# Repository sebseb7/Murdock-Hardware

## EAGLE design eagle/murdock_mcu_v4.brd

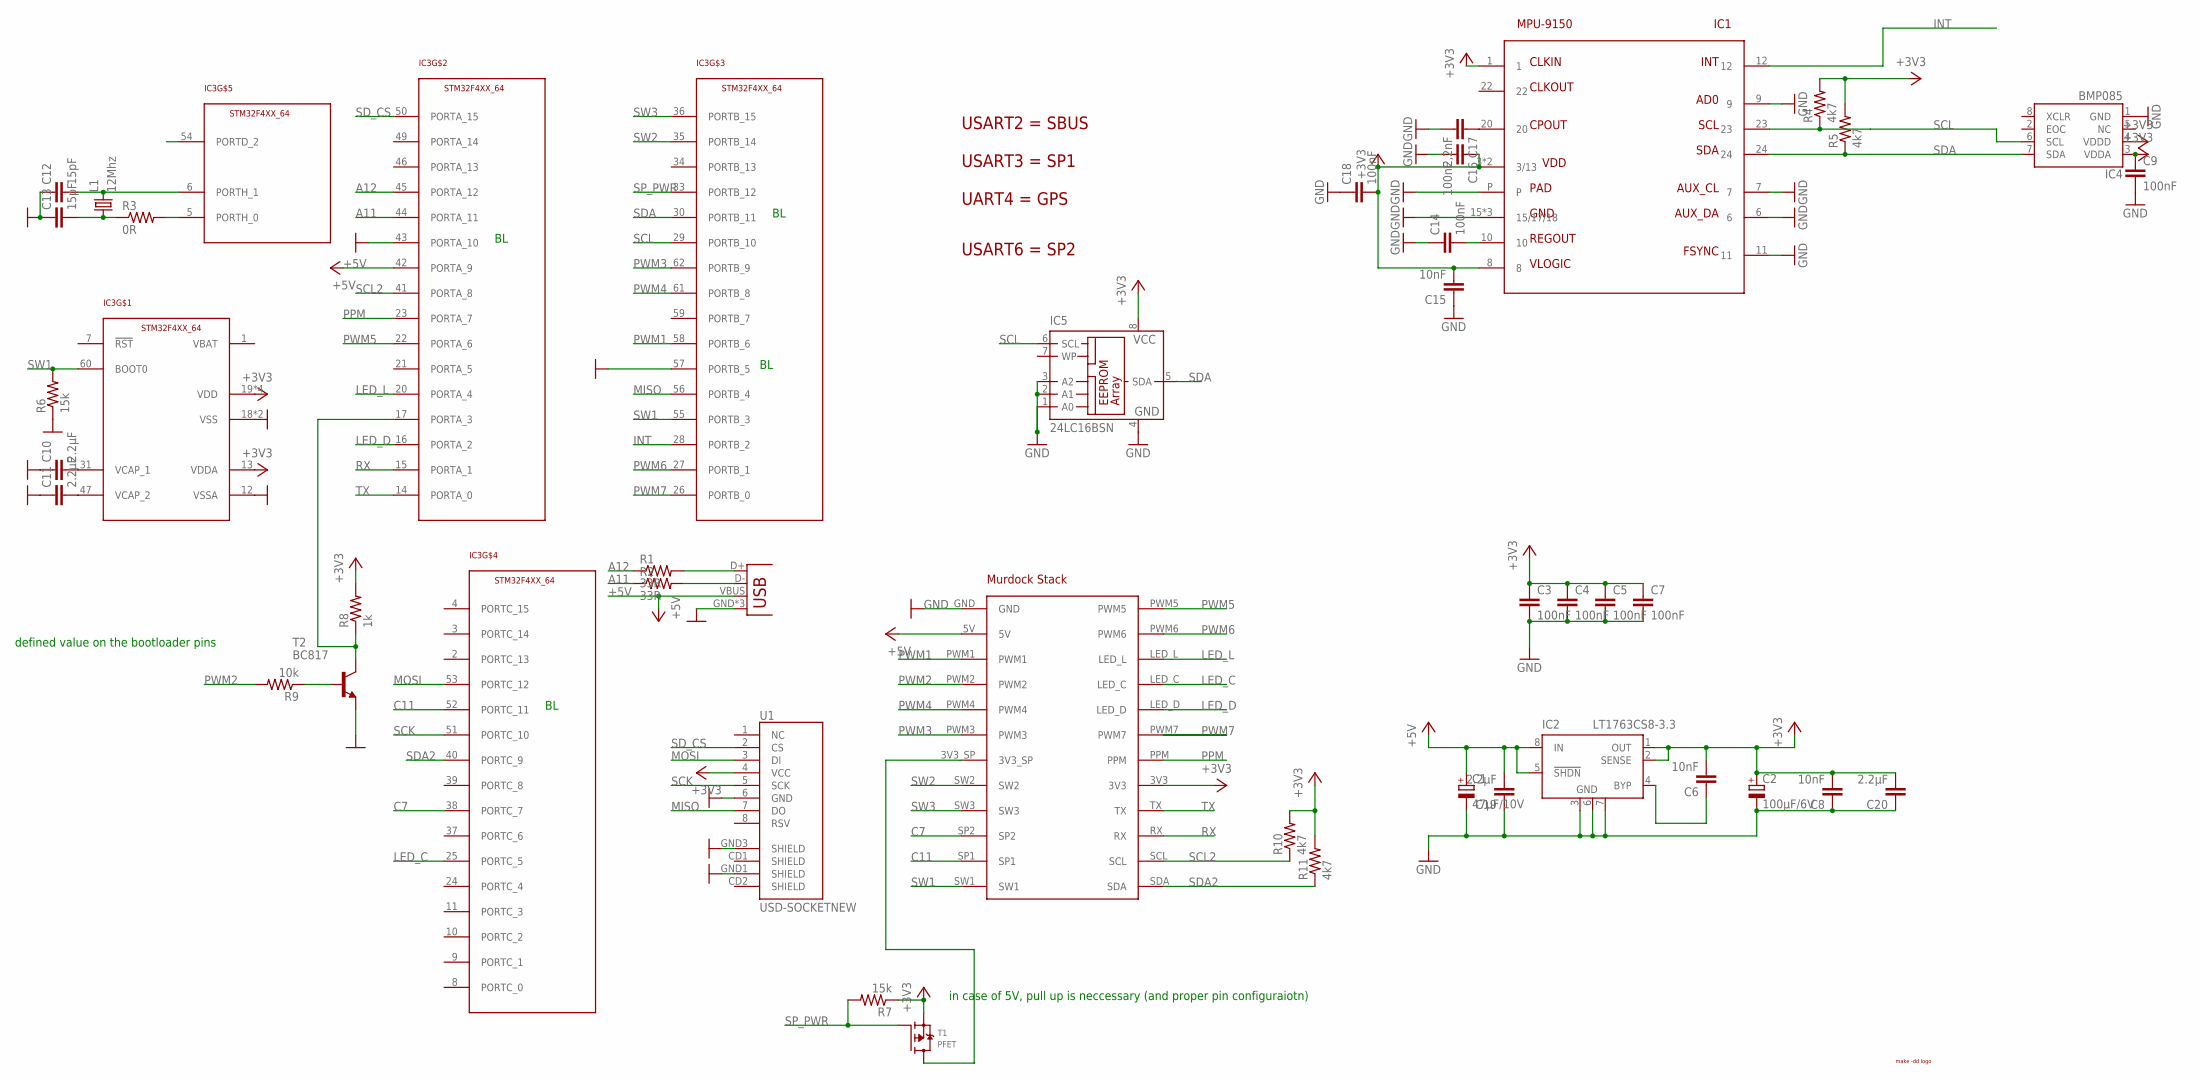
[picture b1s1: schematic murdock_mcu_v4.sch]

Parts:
C1: 47µF/10V; SMC_C
C2: 100µF/6V; SMC_C
C3, C4, C5, C7, C9, C14, C16, C18: 100nF; 0402-CAP
C6, C8: 10nF; C0402
C10, C11, C19, C20: 2.2µF; 0805
C12, C13: 15pF; 0402-CAP
C15: 10nF; 0402-CAP
C17: 2,2nF; 0402-CAP
IC1: MPU-9150; QFN24
IC2: LT1763CS8-3.3; SOIC8
IC3: STM32F4XX_64; TQFP64
IC4: BMP085
IC5: 24LC16BSN; SO-08
JP1: USB-MICROB
L1: 12Mhz; X22
R1, R2: 33R; 0402-RES
R3: 0R; 0402-RES
R4, R5, R10, R11: 4k7; 0402-RES
R6, R7: 15k; 0402-RES
R8: 1k; 0402-RES
R9: 10k; 0402-RES
T1: PFET; SOT23-R
T2: BC817; SOT23
U1: USD-SOCKETNEW; MICRO-SD-SOCKET-PP
U$1: MAKE-DD_LOGO
X2: MURDOCK_STACK

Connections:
+3V3: C2.+, C3.1, C4.1, C5.1, C6.2, C7.1, C8.2, C9.1, C15.2, C16.1, C18.2, C20.2, IC1.1, IC1.3 (3/13), IC1.8, IC1.13 (3/13), IC2.1 (OUT), IC2.2 (SENSE), IC3.13 (VDDA), IC3.19 (VDD), IC3.32 (VDD), IC3.48 (VDD), IC3.64 (VDD), IC4.3 (VDDA), IC4.4 (VDDD), IC5.8 (VCC), R4.2, R5.2, R7.1, R8.2, R10.2, R11.2, T1.2 (S), U1.4 (VCC), X2.3V3
+5V: C1.+, C19.2, IC2.5 (!SHDN), IC2.8 (IN), IC3.42 (PORTA_9), JP1.VBUS, X2.5V
A11: IC3.44 (PORTA_11), R2.1
A12: IC3.45 (PORTA_12), R1.1
C7: IC3.38 (PORTC_7), X2.SP2
C11: IC3.52 (PORTC_11), X2.SP1
GND: C1.-, C2.-, C3.2, C4.2, C5.2, C7.2, C8.1, C9.2, C10.1, C11.1, C12.1, C13.1, C14.1, C15.1, C16.2, C17.2, C18.1, C19.1, C20.1, IC1.6, IC1.7, IC1.9, IC1.11, IC1.15 (15/17/18), IC1.17 (15/17/18), IC1.18 (15/17/18), IC1.P, IC2.3 (GND), IC2.6 (GND), IC2.7 (GND), IC3.12 (VSSA), IC3.18 (VSS), IC3.43 (PORTA_10), IC3.57 (PORTB_5), IC3.63 (VSS), IC4.1 (GND), IC5.1 (A0), IC5.2 (A1), IC5.3 (A2), IC5.4 (GND), JP1.GND, JP1.MT1 (GND), JP1.MT2 (GND), R6.1, T2.2 (E), U1.6 (GND), U1.GND1 (SHIELD), U1.GND3 (SHIELD), X2.GND
INT: IC1.12, IC3.28 (PORTB_2)
LED_C: IC3.25 (PORTC_5), X2.LED_C
LED_D: IC3.16 (PORTA_2), X2.LED_D
LED_L: IC3.20 (PORTA_4), X2.LED_L
MISO: IC3.56 (PORTB_4), U1.7 (DO)
MOSI: IC3.53 (PORTC_12), U1.3 (DI)
unnamed: JP1.D-, R2.2
unnamed: JP1.D+, R1.2
unnamed: C10.2, IC3.31 (VCAP_1)
unnamed: C11.2, IC3.47 (VCAP_2)
unnamed: IC3.5 (PORTH_0), R3.2
unnamed: C13.2, L1.1, R3.1
unnamed: C12.2, IC3.6 (PORTH_1), L1.3 (2)
unnamed: T1.3 (D), X2.3V3_SP
unnamed: C14.2, IC1.10
unnamed: C17.1, IC1.20
unnamed: IC3.17 (PORTA_3), R8.1, T2.3 (C)
unnamed: R9.1, T2.1 (B)
unnamed: C6.1, IC2.4 (BYP)
PPM: IC3.23 (PORTA_7), X2.PPM
PWM1: IC3.58 (PORTB_6), X2.PWM1
PWM2: R9.2, X2.PWM2
PWM3: IC3.62 (PORTB_9), X2.PWM3
PWM4: IC3.61 (PORTB_8), X2.PWM4
PWM5: IC3.22 (PORTA_6), X2.PWM5
PWM6: IC3.27 (PORTB_1), X2.PWM6
PWM7: IC3.26 (PORTB_0), X2.PWM7
RX: IC3.15 (PORTA_1), X2.RX
SCK: IC3.51 (PORTC_10), U1.5 (SCK)
SCL: IC1.23, IC3.29 (PORTB_10), IC4.6 (SCL), IC5.6 (SCL), R4.1
SCL2: IC3.41 (PORTA_8), R10.1, X2.SCL
SDA: IC1.24, IC3.30 (PORTB_11), IC4.7 (SDA), IC5.5 (SDA), R5.1
SDA2: IC3.40 (PORTC_9), R11.1, X2.SDA
SD_CS: IC3.50 (PORTA_15), U1.2 (CS)
SP_PWR: IC3.33 (PORTB_12), R7.2, T1.1 (G)
SW1: IC3.55 (PORTB_3), IC3.60 (BOOT0), R6.2, X2.SW1
SW2: IC3.35 (PORTB_14), X2.SW2
SW3: IC3.36 (PORTB_15), X2.SW3
TX: IC3.14 (PORTA_0), X2.TX

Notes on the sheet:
defined value on the bootloader pins
UART4 = GPS
USART2 = SBUS
USART6 = SP2
USART3 = SP1
in case of 5V, pull up is neccessary (and proper pin configuraiotn)

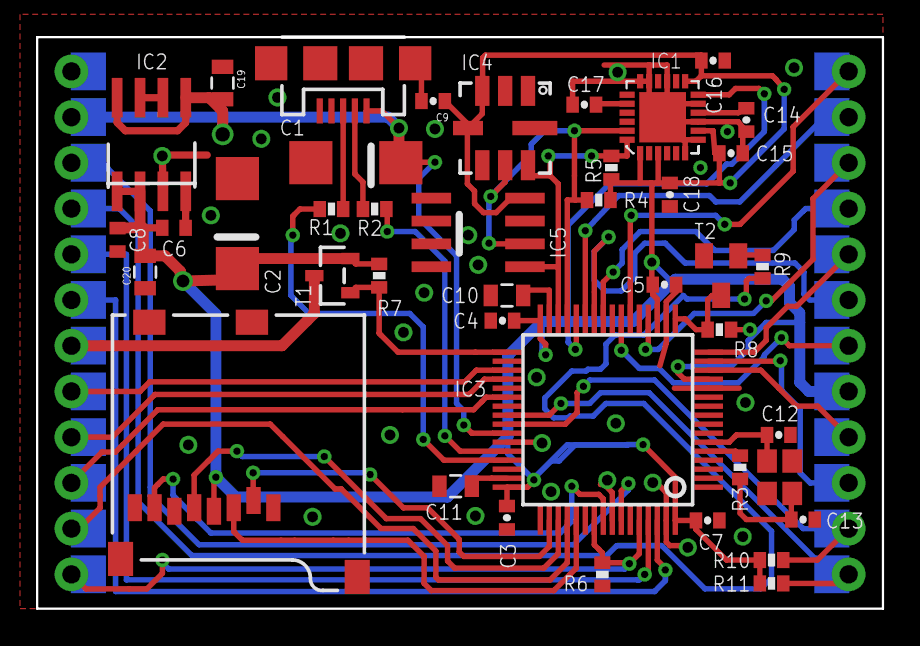
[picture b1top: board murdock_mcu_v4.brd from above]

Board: 2 copper layers, 47.0 x 31.8 mm, 43 parts (1 on the bottom side), 46 nets.

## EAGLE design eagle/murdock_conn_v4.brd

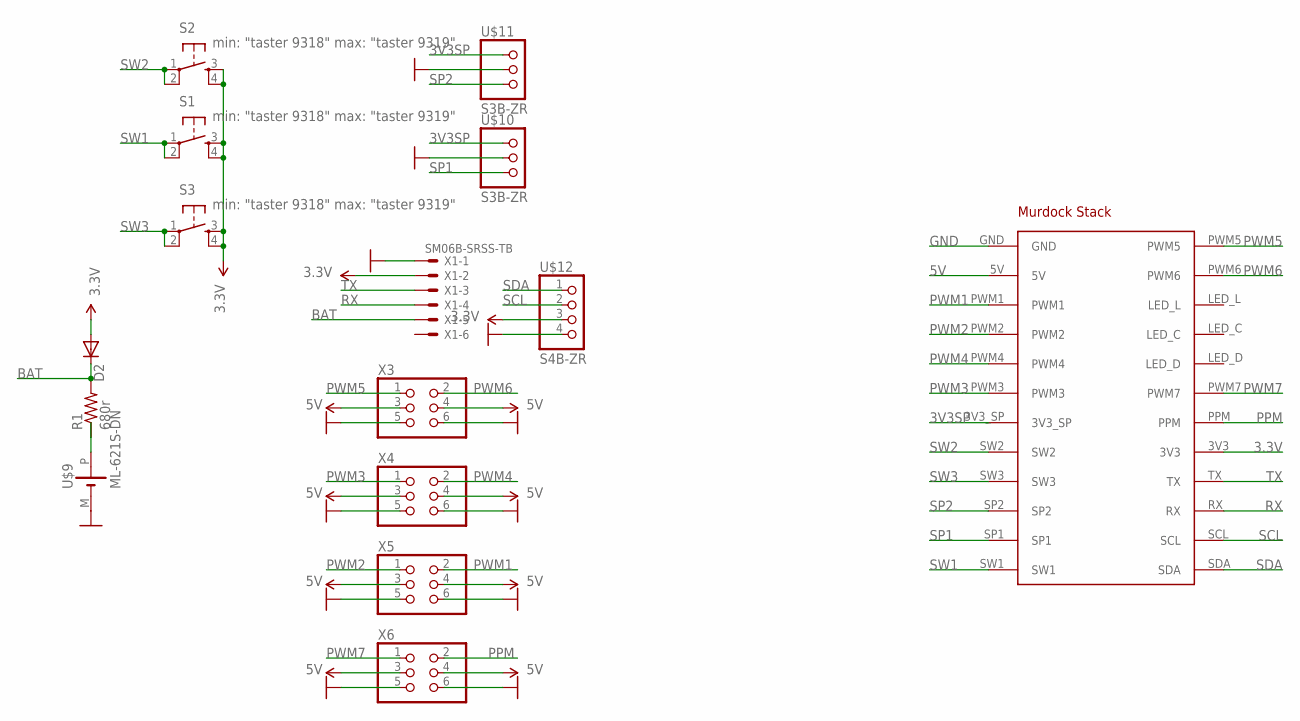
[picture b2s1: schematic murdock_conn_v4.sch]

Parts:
D2: DIODE-SOD323-R; SOD323-R
R1: 680r; 0805
S1, S2, S3: min: "taster 9318" max: "taster 9319"; LSH
U$9: ML-621S-DN
U$10, U$11: S3B-ZR
U$12: S4B-ZR
X1: SM06B-SRSS-TB
X3, X4, X5, X6: PINHD-2X3/90; 2X03/90
X7: MURDOCK_STACK

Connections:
3.3V: D2.A, S1.3, S1.4, S2.3, S2.4, S3.3, S3.4, U$12.3, X1.2, X7.3V3
3V3SP: U$10.1, U$11.1, X7.3V3_SP
5V: X3.3, X3.4, X4.3, X4.4, X5.3, X5.4, X6.3, X6.4, X7.5V
BAT: D2.C, R1.2, X1.5
GND: U$9.M (-), U$10.2, U$11.2, U$12.4, X1.1, X3.5, X3.6, X4.5, X4.6, X5.5, X5.6, X6.5, X6.6, X7.GND
unnamed: R1.1, U$9.P (+)
PPM: X6.2, X7.PPM
PWM1: X5.2, X7.PWM1
PWM2: X5.1, X7.PWM2
PWM3: X4.1, X7.PWM3
PWM4: X4.2, X7.PWM4
PWM5: X3.1, X7.PWM5
PWM6: X3.2, X7.PWM6
PWM7: X6.1, X7.PWM7
RX: X1.4, X7.RX
SCL: U$12.2, X7.SCL
SDA: U$12.1, X7.SDA
SP1: U$10.3, X7.SP1
SP2: U$11.3, X7.SP2
SW1: S1.1, S1.2, X7.SW1
SW2: S2.1, S2.2, X7.SW2
SW3: S3.1, S3.2, X7.SW3
TX: X1.3, X7.TX

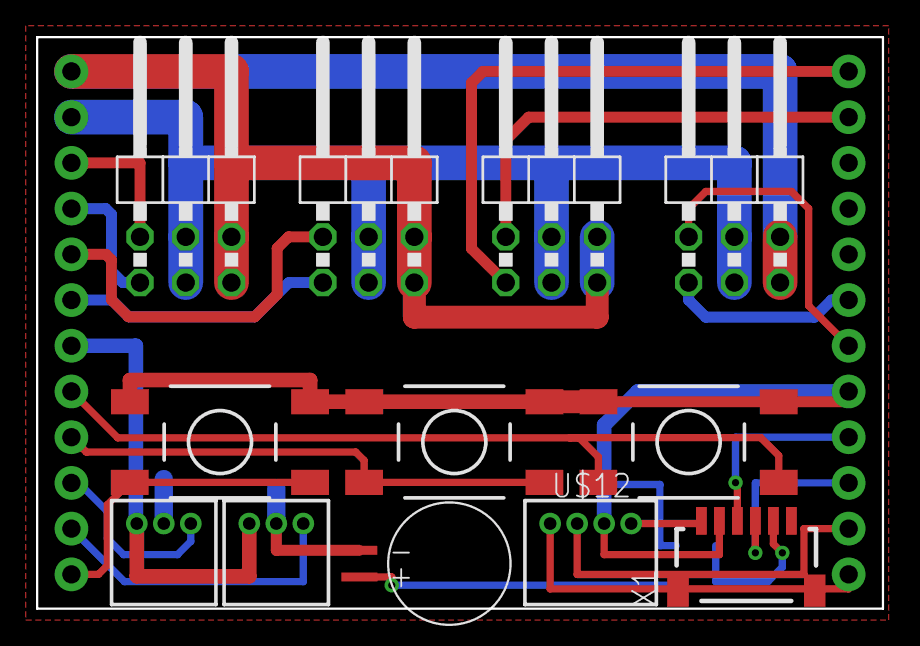
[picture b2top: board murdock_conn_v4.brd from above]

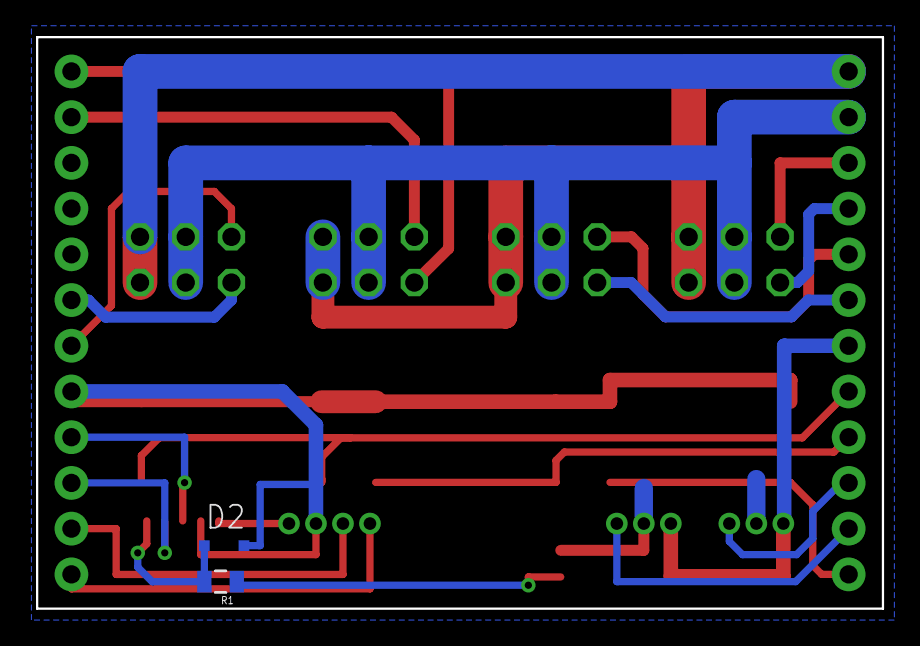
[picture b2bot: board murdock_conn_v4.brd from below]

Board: 2 copper layers, 47.0 x 31.8 mm, 15 parts (2 on the bottom side), 23 nets.

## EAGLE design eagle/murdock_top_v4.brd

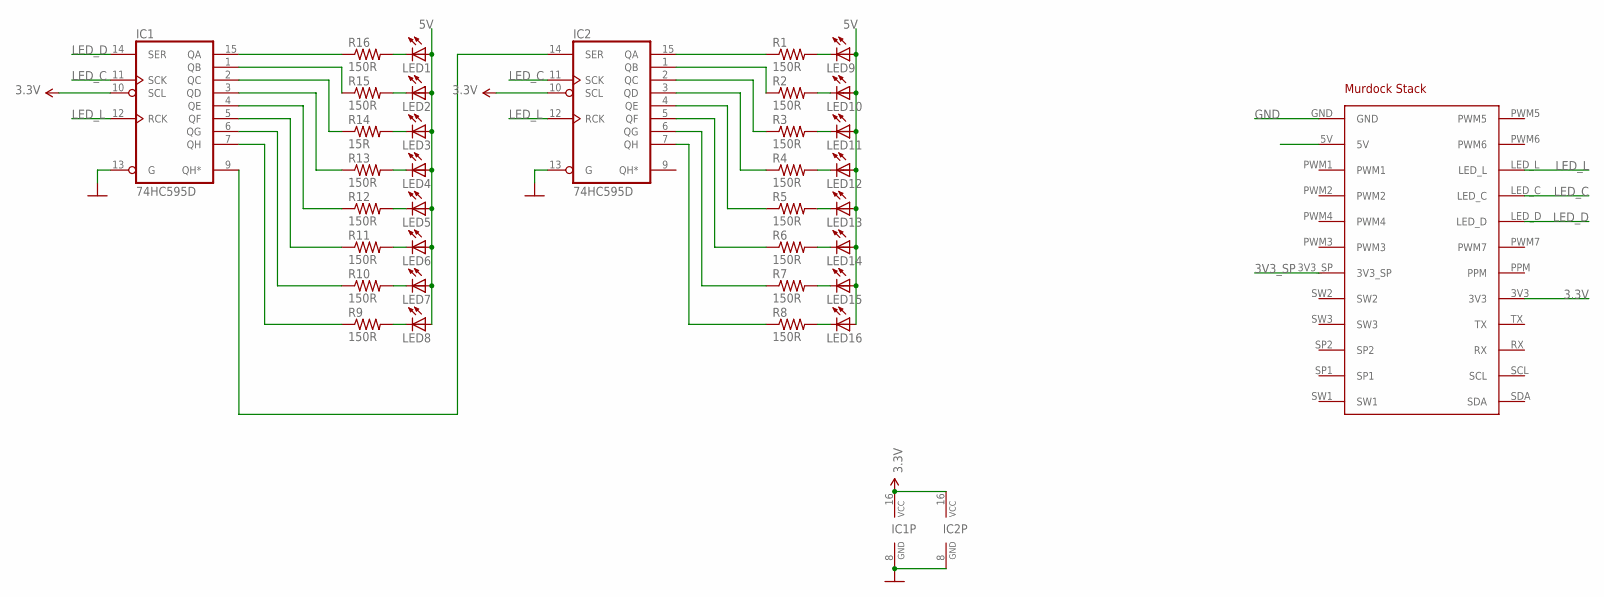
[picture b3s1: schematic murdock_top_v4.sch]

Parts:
IC1, IC2: 74HC595D; SO16
LED1, LED2, LED3, LED4, LED5, LED6, LED7, LED8, LED9, LED10, LED11, LED12, LED13, LED14, LED15, LED16: LGM47K
R1, R2, R3, R4, R5, R6, R7, R8, R9, R10, R11, R12, R13, R15, R16: 150R; 0402-RES
R14: 15R; 0402-RES
X1: MURDOCK_STACK

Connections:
3.3V: IC1.10 (SCL), IC1.16 (VCC), IC2.10 (SCL), IC2.16 (VCC), X1.3V3
3V3_SP: X1.3V3_SP
5V: LED1.A, LED2.A, LED3.A, LED4.A, LED5.A, LED6.A, LED7.A, LED8.A, LED9.A, LED10.A, LED11.A, LED12.A, LED13.A, LED14.A, LED15.A, LED16.A, X1.5V
GND: IC1.8 (GND), IC1.13 (G), IC2.8 (GND), IC2.13 (G), X1.GND
LED_C: IC1.11 (SCK), IC2.11 (SCK), X1.LED_C
LED_D: IC1.14 (SER), X1.LED_D
LED_L: IC1.12 (RCK), IC2.12 (RCK), X1.LED_L
unnamed: IC1.9 (QH*), IC2.14 (SER)
unnamed: LED9.K (C), R1.2
unnamed: LED10.K (C), R2.2
unnamed: LED11.K (C), R3.2
unnamed: LED12.K (C), R4.2
unnamed: LED13.K (C), R5.2
unnamed: LED14.K (C), R6.2
unnamed: LED15.K (C), R7.2
unnamed: LED16.K (C), R8.2
unnamed: LED1.K (C), R16.2
unnamed: LED2.K (C), R15.2
unnamed: LED3.K (C), R14.2
unnamed: LED4.K (C), R13.2
unnamed: LED5.K (C), R12.2
unnamed: LED6.K (C), R11.2
unnamed: LED7.K (C), R10.2
unnamed: LED8.K (C), R9.2
Q0: IC2.15 (QA), R1.1
Q1: IC2.1 (QB), R2.1
Q2: IC2.2 (QC), R3.1
Q3: IC2.3 (QD), R4.1
Q4: IC2.4 (QE), R5.1
Q5: IC2.5 (QF), R6.1
Q6: IC2.6 (QG), R7.1
Q7: IC2.7 (QH), R8.1
QA: IC1.15 (QA), R16.1
QB: IC1.1 (QB), R15.1
QC: IC1.2 (QC), R14.1
QD: IC1.3 (QD), R13.1
QE: IC1.4 (QE), R12.1
QF: IC1.5 (QF), R11.1
QG: IC1.6 (QG), R10.1
QH: IC1.7 (QH), R9.1

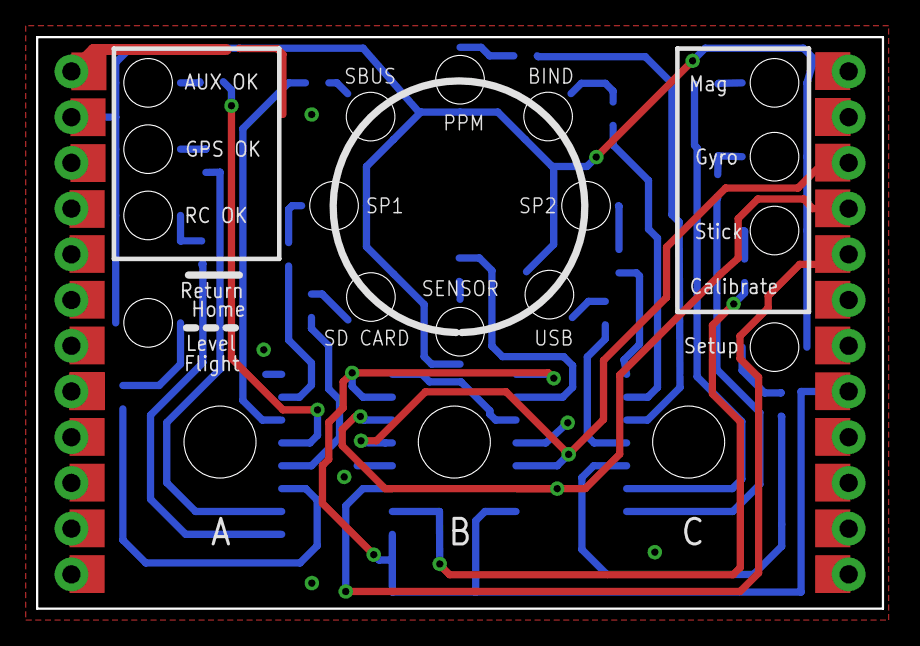
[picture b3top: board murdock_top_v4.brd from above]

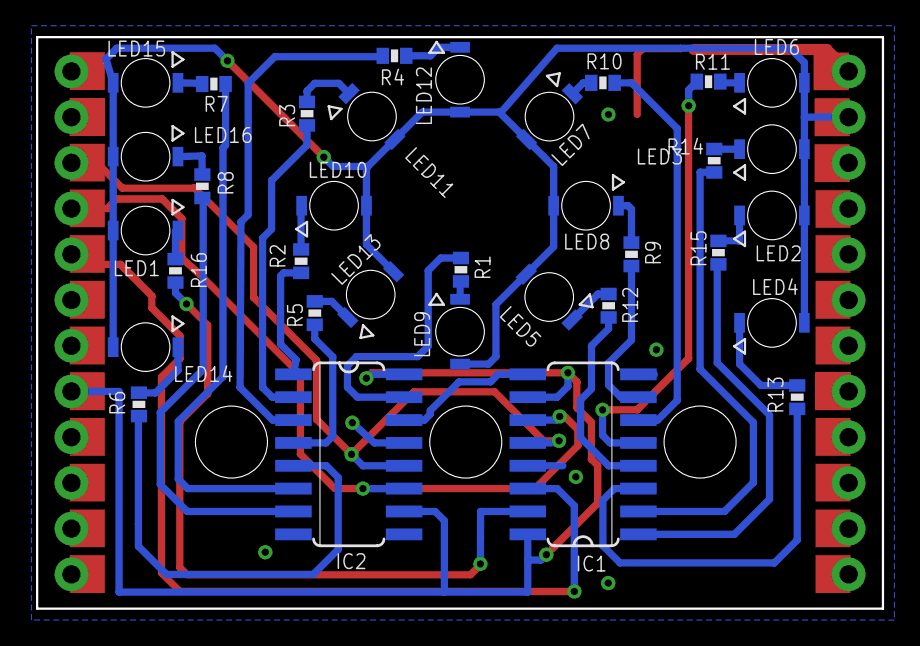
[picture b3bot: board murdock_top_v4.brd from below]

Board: 2 copper layers, 47.0 x 31.8 mm, 35 parts (34 on the bottom side), 39 nets.

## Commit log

2012-05-28 pre v1
2012-05-28 ignorance
2012-05-28 misc
2012-10-24 new version; still in progress
2012-10-28 LED positions beautified
2012-12-13 better fast inv sqrt
2013-01-26 power and pwm routing
2013-01-26 more routing
2013-01-26 final fixes for 1st production run
2013-01-26 moved
2013-01-26 now working on v2
2013-01-26 updated labels
2013-01-26 readme & picture
2013-01-26 smaller updates
2013-01-26 updated stack schematic
2013-01-26 values
2013-02-03 increaded button holes
2013-02-03 note
2013-02-03 improved pads
2013-02-03 usb placement & smaller tantal
2013-02-03 moved v2 in folder
2013-02-03 moved servo connectors
2013-02-03 bootloader robustness
2013-02-04 pwm/sbus to new pin @usart2 & led_l moved
2013-02-04 added eeprom
2013-02-04 usb fix
2013-02-04 moved sd card
2013-02-06 wireless trainer/student system based on murdock
2013-02-06 smaller changes
2013-02-06 mirrored spektrum & moved buttons
2013-02-06 updates preview image
2013-02-06 text orientation
2013-02-07 conneced LEDs to switche 3v3
2013-02-07 typo
2013-02-08 updated silk
2013-02-08 switch part-numbers
2013-02-13 merge
2013-02-13 more led names
2013-02-13 moved files
2013-02-13 invert sbus
2013-02-13 final touches
2013-02-14 v4 hardware: differend GPS/OSD connectors
2013-04-17 minor stuff

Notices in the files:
parts and their libraries:
SparkFun-Passives: Licensing: CC v3.0 Share-Alike You are welcome to use this library for commercial purposes.
microbuilder: This work is placed in the public domain, and may be freely used for commercial and non-commercial work with the following conditions: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
